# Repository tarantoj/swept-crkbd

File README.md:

# Swept Corne
## This board designed is now stable and has reached maintenance mode.

## What is the swept corne?

The Swept Corne is a mix between the [Sweep](https://github.com/davidphilipbarr/Sweep) (which is itself a version of the [Ferris](https://github.com/pierrechevalier83/ferris)) and the [Corne](https://github.com/foostan/crkbd).

## Motivation

I made the jump from a 60% qwerty keyboard to colemak mod-dh on a sweep. After getting up to speed both with the new layout and form factor I realized that to reach peak productivity I'd need a few more keys and the corne was the obvious choice but the non-choc spacing,
lack support for a power switch and the less aggresive staggering made me miss the sweep, so I decided to take the sweep as a starting point and add the extra keys by keeping it wireless friendly. The [Corne-is Zen](https://lowprokb.ca/products/corne-ish-zen) has similar
goals but up to this point has only been available through group buys and is closed source.

## What are the different types?

There's currently only one version of the swept with choc spacing as well as an on-off switch and no TRRS connector, this is to have the reset switch in a more comfortable position.

## Components list

To build and use a Swept you will need

* 1x PCB Kit (Instructions on how to order below).
* 2 nice!nanos. [Typeractive](https://typeractive.xyz/) has good prices, as well as fast shipping and processing.
* 2 batteries. From [Typeractive](https://typeractive.xyz/products/lithium-battery-110mah).
* 2 Mill-Max sockets with pins. Make sure you get the high-profile ones, low-profile still fits a battery underneath but there's less space. [Typeractive](https://typeractive.xyz/products/machine-sockets-and-pins) carries the correct size.
* 42 Choc v1 switches. You can get them from [MKUltra](https://mkultra.click/choc-switches).
* 84 Mill-Max 3305 or 7305 sockets, you can get either model from [prevailkey](https://prevailkeyco.com/products/3305-mill-max-sockets?variant=42568596193534). These are optional but you can use them to make your board hot-swap. I recommend getting some extra ones because they're very easy to lose.
* 42 smd diodes. From [MKUltra](https://mkultra.click/diode-1n4148-sod-123f/) for flush SOD-123F form factor, or from [Boardsource](https://boardsource.xyz/store/5ec9fc5d64caf04f83aa646c) for glass smd form factor; the former ones might be easier to solder for some people. I recommend getting some extra ones because they're very easy to lose.
* 42 keycaps. You can get them from [MKUltra](https://mkultra.click/mbk-choc-keycaps) or [Boardsource](https://boardsource.xyz/store/5f6ef2d68e3bf05ab838f918). I recommend getting a least a couple of homing keys, available from both providers.
* 2x reset switches ([B3U-1000P(M)](https://github.com/davidphilipbarr/Sweep/issues/20)). [This kit](https://www.amazon.com/dp/B07LCBLB8N?psc=1&ref=ppx_yo2ov_dt_b_product_details) includes switches that fit.
* Rubber feet, [these](https://www.amazon.com/dp/B07CNQC695?psc=1&ref=ppx_yo2ov_dt_b_product_details) work great.
* 2x power switches. [these](https://www.amazon.com/Gikfun-Switch-Toggle-Arduino-AE1073/dp/B01GFFGA4I/ref=psdc_495324_t1_B07SJWWYZP) work great.
* 1 USB C cable.

Note: All purchase links are for the US, PRs with links for other countries are welcome.

## Ordering The PCB

To order the PCB the following settings are recommended: 

|Detail|Value|
|---|---|
|Gerber file|`Swept_Y_vX.zip` where Y stands for variation and X stands for version|
|Base material|FR-4|
|Layers|2|
|Dimension| Depends on the board, this is picked up automatically by JLCPCB|
|Different design|2|
|Delivery format|Panel by customer|
|PCB thickness|1.6mm|
|PCB color|(Personal preference)|
|Silkscreen|(Personal preference)|
|Surface finish|(Personal preference)|
|Outer copper weight|1oz|
|Gold Fingers|No|
|Confirm production file|No|
|Castellated holes|No|
|Remove order number|Yes|

Find the different versions on the releases page.

1: Settings are for [JLCPCB](https://jlcpcb.com/), but could work for other manufacturers.

2: Settings are taken from [Kyek's video guide](https://www.youtube.com/watch?v=fBPu7AyDtkM&t=17s).

## How do I make this thing?

Build video coming soon.

## What if I want one but I don't want to build it?

Visit [my Etsy shop](https://www.etsy.com/listing/1235225784/custom-swept-corne-split-wireless) to get one built by me.

## Firmware

Firmware for zmk and nice!nano is called ["Corne"](https://zmk.dev/docs/hardware/).

[My personal configuration](https://github.com/AYM1607/corne-zmk-config). Tested on the v0.1 version.

## Changelog

### v1.1.1 (Recommended version)

- Added extra mountig holes for ease of case design.

### v1.1.0 

- Added support for the [nice!view](https://nicekeyboards.com/nice-view) sharp memory displays. You don't need it to build a keyboard, it's completely optional.

### v1.0.0 

- Boards now have optional support for Kailh choc hot-swap sockets.
- The form factor is not exactly the same to accomodate the sockets.

### v0.2.0

- Introduced the Swept Corne 3x5
- All the diodes now face the same way on both boards.

### v0.1.2 

- Updated silk screen to make the battery polarity easier to read.

### v0.1.1

- Deleted extra holes from the switch footprint which might be causing manufacturers to charge extra.

### v0.1

Differences from the original Sweep:
- Added an extra pinky column.
- Added an extra thumb key.
- Converted from direct to switch connections to matrix with diodes keeping compatibility with the corne.

The following versioning schema will be followed as closely as possible.
- Major versions: Changes to the form factor.
- Minor versions: Changes that affect the build processs, e.g. Position or orientation of components.
- Patch versions: No change to the build process.

## Who made this?

* [AYM1607](https://github.com/AYM1607)

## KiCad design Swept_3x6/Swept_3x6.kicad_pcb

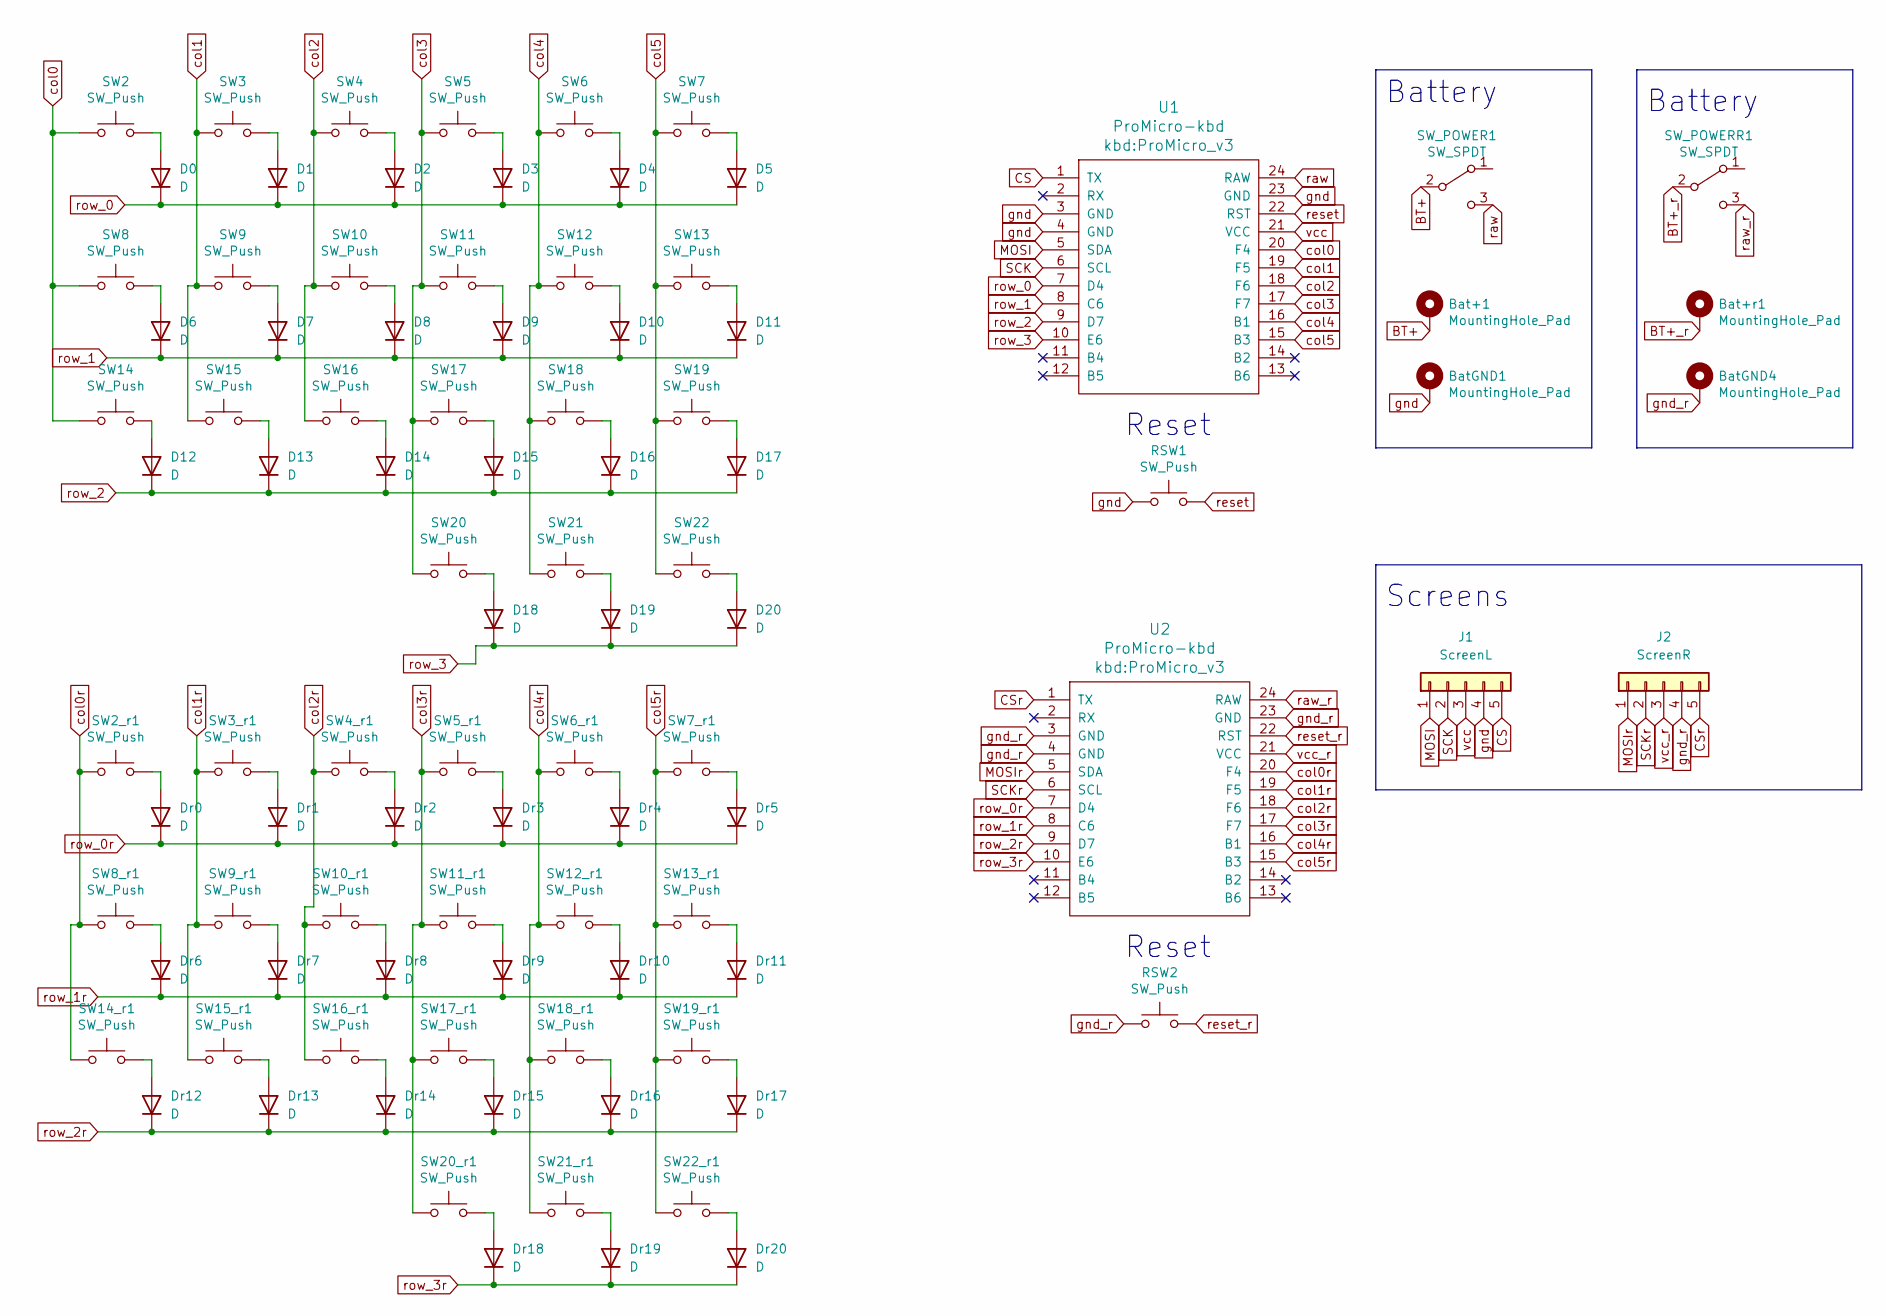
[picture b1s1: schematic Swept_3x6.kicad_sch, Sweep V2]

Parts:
Bat+1: MountingHole_Pad; 1pin_conn
Bat+r1: MountingHole_Pad; 1pin_conn
BatGND1, BatGND4: MountingHole_Pad; 1pin_conn
D0, D1, D2, D3, D4, D5, D6, D7, D8, D9, D10, D11, D12, D13, D14, D15, D16, D17, D18, D19, D20: D; D3_SMD_v2; LCSC C2099
Dr0, Dr1, Dr2, Dr3, Dr4, Dr5, Dr6, Dr7, Dr8, Dr9, Dr10, Dr11, Dr12, Dr13, Dr14, Dr15, Dr16, Dr17, Dr18, Dr19, Dr20: D; D3_SMD_v2; LCSC C2099
J1: ScreenL; PinHeader_1x05_P2.54mm_Vertical
J2: ScreenR; PinHeader_1x05_P2.54mm_Vertical
RSW1, RSW2: SW_Push; ResetSW
SW2, SW2_r1, SW3, SW3_r1, SW4, SW4_r1, SW5, SW5_r1, SW6, SW6_r1, SW7, SW7_r1, SW8, SW8_r1, SW9, SW9_r1, SW10, SW10_r1, SW11, SW11_r1, SW12, SW12_r1, SW13, SW13_r1, SW14, SW14_r1, SW15, SW15_r1, SW16, SW16_r1, SW17, SW17_r1, SW18, SW18_r1, SW19, SW19_r1, SW20, SW20_r1, SW21, SW21_r1, SW22, SW22_r1: SW_Push; Kailh_socket_PG1350_optional
SW_POWER1: SW_SPDT; SW_SPDT_PCM12
SW_POWERR1: SW_SPDT; SW_SPDT_PCM12
U1, U2: ProMicro-kbd; ProMicro_v3

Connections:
BT+: Bat+1.1, SW_POWER1.2 (B)
BT+_r: Bat+r1.1, SW_POWERR1.2 (B)
CS: J1.5, U1.1 (TX)
CSr: J2.5, U2.1 (TX)
MOSI: J1.1, U1.5 (SDA)
MOSIr: J2.1, U2.5 (SDA)
unnamed: D0.2 (A), SW2.2
unnamed: D1.2 (A), SW3.2
unnamed: D2.2 (A), SW4.2
unnamed: D3.2 (A), SW5.2
unnamed: D4.2 (A), SW6.2
unnamed: D5.2 (A), SW7.2
unnamed: D6.2 (A), SW8.2
unnamed: D7.2 (A), SW9.2
unnamed: D8.2 (A), SW10.2
unnamed: D9.2 (A), SW11.2
unnamed: D10.2 (A), SW12.2
unnamed: D11.2 (A), SW13.2
unnamed: D12.2 (A), SW14.2
unnamed: D13.2 (A), SW15.2
unnamed: D14.2 (A), SW16.2
unnamed: D15.2 (A), SW17.2
unnamed: D16.2 (A), SW18.2
unnamed: D17.2 (A), SW19.2
unnamed: D18.2 (A), SW20.2
unnamed: D19.2 (A), SW21.2
unnamed: D20.2 (A), SW22.2
unnamed: Dr0.2 (A), SW2_r1.2
unnamed: Dr1.2 (A), SW3_r1.2
unnamed: Dr2.2 (A), SW4_r1.2
unnamed: Dr3.2 (A), SW5_r1.2
unnamed: Dr4.2 (A), SW6_r1.2
unnamed: Dr5.2 (A), SW7_r1.2
unnamed: Dr6.2 (A), SW8_r1.2
unnamed: Dr7.2 (A), SW9_r1.2
unnamed: Dr8.2 (A), SW10_r1.2
unnamed: Dr9.2 (A), SW11_r1.2
unnamed: Dr10.2 (A), SW12_r1.2
unnamed: Dr11.2 (A), SW13_r1.2
unnamed: Dr12.2 (A), SW14_r1.2
unnamed: Dr13.2 (A), SW15_r1.2
unnamed: Dr14.2 (A), SW16_r1.2
unnamed: Dr15.2 (A), SW17_r1.2
unnamed: Dr16.2 (A), SW18_r1.2
unnamed: Dr17.2 (A), SW19_r1.2
unnamed: Dr18.2 (A), SW20_r1.2
unnamed: Dr19.2 (A), SW21_r1.2
unnamed: Dr20.2 (A), SW22_r1.2
SCK: J1.2, U1.6 (SCL)
SCKr: J2.2, U2.6 (SCL)
col0: SW2.1, SW8.1, SW14.1, U1.20 (F4)
col0r: SW2_r1.1, SW8_r1.1, SW14_r1.1, U2.20 (F4)
col1: SW3.1, SW9.1, SW15.1, U1.19 (F5)
col1r: SW3_r1.1, SW9_r1.1, SW15_r1.1, U2.19 (F5)
col2: SW4.1, SW10.1, SW16.1, U1.18 (F6)
col2r: SW4_r1.1, SW10_r1.1, SW16_r1.1, U2.18 (F6)
col3: SW5.1, SW11.1, SW17.1, SW20.1, U1.17 (F7)
col3r: SW5_r1.1, SW11_r1.1, SW17_r1.1, SW20_r1.1, U2.17 (F7)
col4: SW6.1, SW12.1, SW18.1, SW21.1, U1.16 (B1)
col4r: SW6_r1.1, SW12_r1.1, SW18_r1.1, SW21_r1.1, U2.16 (B1)
col5: SW7.1, SW13.1, SW19.1, SW22.1, U1.15 (B3)
col5r: SW7_r1.1, SW13_r1.1, SW19_r1.1, SW22_r1.1, U2.15 (B3)
gnd: BatGND1.1, J1.4, RSW1.1, U1.3 (GND), U1.4 (GND), U1.23 (GND)
gnd_r: BatGND4.1, J2.4, RSW2.1, U2.3 (GND), U2.4 (GND), U2.23 (GND)
raw: SW_POWER1.3 (C), U1.24 (RAW)
raw_r: SW_POWERR1.3 (C), U2.24 (RAW)
reset: RSW1.2, U1.22 (RST)
reset_r: RSW2.2, U2.22 (RST)
row_0: D0.1 (K), D1.1 (K), D2.1 (K), D3.1 (K), D4.1 (K), D5.1 (K), U1.7 (D4)
row_0r: Dr0.1 (K), Dr1.1 (K), Dr2.1 (K), Dr3.1 (K), Dr4.1 (K), Dr5.1 (K), U2.7 (D4)
row_1: D6.1 (K), D7.1 (K), D8.1 (K), D9.1 (K), D10.1 (K), D11.1 (K), U1.8 (C6)
row_1r: Dr6.1 (K), Dr7.1 (K), Dr8.1 (K), Dr9.1 (K), Dr10.1 (K), Dr11.1 (K), U2.8 (C6)
row_2: D12.1 (K), D13.1 (K), D14.1 (K), D15.1 (K), D16.1 (K), D17.1 (K), U1.9 (D7)
row_2r: Dr12.1 (K), Dr13.1 (K), Dr14.1 (K), Dr15.1 (K), Dr16.1 (K), Dr17.1 (K), U2.9 (D7)
row_3: D18.1 (K), D19.1 (K), D20.1 (K), U1.10 (E6)
row_3r: Dr18.1 (K), Dr19.1 (K), Dr20.1 (K), U2.10 (E6)
vcc: J1.3, U1.21 (VCC)
vcc_r: J2.3, U2.21 (VCC)

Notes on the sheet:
Reset
Battery
Screens

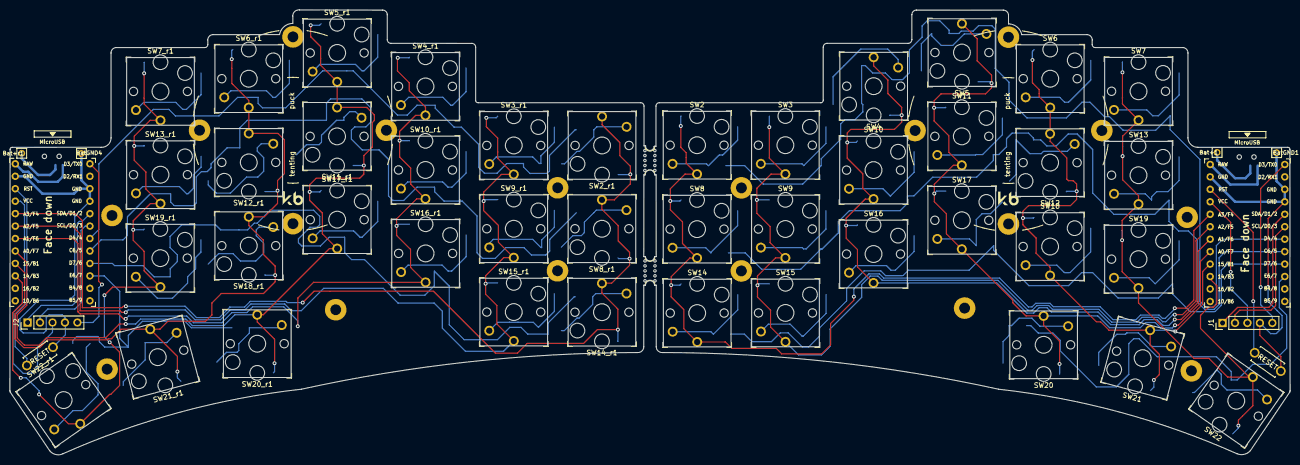
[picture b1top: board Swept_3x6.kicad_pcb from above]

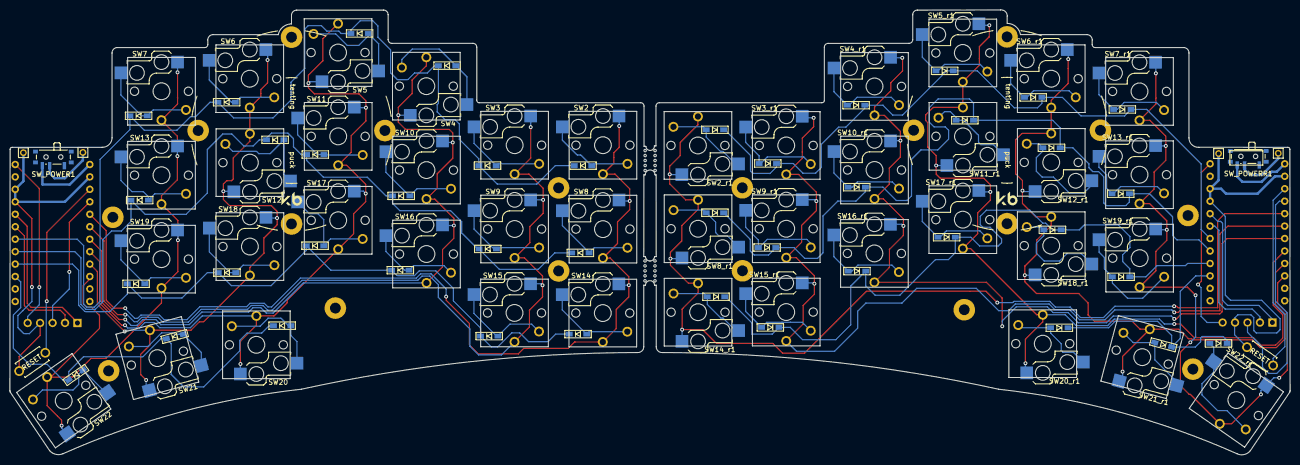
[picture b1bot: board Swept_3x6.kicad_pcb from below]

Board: 2 copper layers, 261.0 x 90.6 mm, 98 parts (44 on the bottom side), 78 nets.

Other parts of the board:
mouse-bite-2mm-slot, mouse-bite-2mm-slot#2: VAL**; mouse-bite-5mm-slot-with-space-for-track

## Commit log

2022-05-29 Update README.
2022-05-29 Schematic finished, pcb ready to route.
2022-05-30 Done with routing.
2022-05-30 Updates gitignore.
2022-05-30 Generated gerber and zip.
2022-05-30 Update readme and moved gerber zip to root.
2022-05-30 Fix readme typo.
2022-06-04 Deleted extra unused holes from the switch footrprint.
2022-06-04 Updated changelog.
2022-06-07 Added extra pictures to the README.
2022-06-07 Remove the untested comments.
2022-06-07 Added link to my personal config in the README.
2022-06-07 Add new line.
2022-06-13 Fix typo and add purchase link?
2022-06-20 Add footprint lib to the repo
2022-06-20 Update release description
2022-06-23 Version 0.2.0
2022-06-23 Updated README for new version
2022-06-23 Added versioning schema
2022-07-05 Added keyswitches.pretty submodule
2022-07-05 Added support for Kailh hot-swap sockets.
2022-07-05 Updated changelog for the new version.
2022-07-10 Added footprint for MS88SF31
2022-12-11 Added nice!view suppor for 3x6
2022-12-12 Added nice!view support for 3x5
2022-12-12 v1.1.0
2023-01-31 Version 1.1.1 of the 3x6 swept.
2023-01-31 Added v1.1.1 to changelog
2023-02-05 Cases up to v1.1.1
2024-10-03 add alternate case
2024-10-06 increase size for rubber pads and add step file
2025-03-08 stuff
